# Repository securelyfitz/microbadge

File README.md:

# microbadge
functional badge in 1 square centimeter

The [Shitty Add-On(SAO) spec](https://hackaday.io/project/52950-defcon-26-shitty-add-ons) made it even easier to build badges, boards, and all sorts of assorted flashy swag without the commitment to building a full badge.

To comlpiment the assortment of SAO boards I was working on, I decided to create the smallest possible functional 'badge' with a single SAO connector.

[Hardware design](#hardware-design) will tell you more about how the badge was designed and built. [Other Components](#other-components) will list the other boards available that can be combined to make up a full 'badge'. [Building your Badge](#building-your-badge) covers how to put pieces together and still have a good chance of them working properly. Finally,  [Programming your Badge](#programming-your-badge) covers how to set up the IDE and rewrite the code on your microbadge via USB.

# Stupid SAO tricks
To push the limits of the SAO, I have two example sketches that output mostly-valid IIC data, but manage to push out completely different protocols at the same time.

## IIC Protocol Polyglots
IIC is a two-wire, multi-master protocol. Devices 'claim' the bus with a start condition, and then transmit an address of a slave which is expected to respond. 
However:
1. The start condition prohibits others from speaking
2. everyone is supposed to ignore the data line while clock is low
This means we can do whatever the heck we want with the data line at that point in time. My two POCs are driving Neopixel displays and transmitting UART, potentially for an opticspy to pick it up over an LED.

[NeoPixel Over IIC](https://github.com/securelyfitz/Adafruit_NeoPixel_Over_IIC)

[SAO OpticSpeaker]

# Hardware Design
The microbadge is based on the [Digispark](http://digistump.com/), a small attiny85 badged arduino-compatible development board that uses the [micronucleus usb bootloader](https://github.com/micronucleus/micronucleus).

## Trimming down the design
The fun objective was to see how small the board really could be, while still being programmable with no special hardware:
1. The Digispark had a USB-A connector made from a thick PCB. This took up space and required especially thick boards. I replaced it with a much smaller microUSB header
1. The Digispark has a large 3.3v regulator to power the attiny85 as well as some add-on devices. It also needed zener diodes to make sure the USB data lines did not exceed 3.3v. I removed both. The board no longer gets power from USB and must have an exernal 3.3v power supply
## Adding to the design
1. The Digispark could get power from USB, or from 3.3 or 5v pins. Without the regulator and no room for additional pins, I added pads on the end to edge-mount a vertical cr2032 holder. It's rather difficult to attach and potentially weak unless reinforced, so several battery-bearing add-ons seem to be a better choice.
1. The digispark had a 6-pin header. the SAO header only needs power, ground, and 2 data pins for I2C.

The SAO connector took the most space and is placed on the same side as the necessary resistors and capacitors, while the attiny and usb micro connctor could fit on the other side.

Thanks to a reel of odd-sku attiny85s and parts from china, the BOM cost was under $1 per microbadge (arms/addons excluded). I originally planned to assemble overseas, but when the quoted timeline was weeks longer than I expected, I reached out to [Piotr](https://github.com/esden) and tricked him into helping with assembly. Despite my poor DFM skills, he still managed to get 1100 of them assembled in time for defcoin. Thank [Piotr](https://twitter.com/esden) and/or [1BitSquared](https://twitter.com/1BitSquared)

# Other components
Building the microbadge was inspired by all the add-ons that were available. I started with a series of arms, then added a few faces, and finally a few addons and adapters:
## [Arms](https://github.com/securelyfitz/sao-arms) 
* human
* robo1 - straight roboto arms
* robo2 - bent robot arms
* tent1 - straight tentacles
* tent2 - bent tentacles
* bug1 - straight bug arms
* bug2 - bent bug arms
## [Faces](https://github.com/securelyfitz/sao-faces)
* terminator to terminate your I2C signals with pullups
* badgewife for badgelife diehards
* smiley for dade murphy fans
## Addons/adapters
* [sao-iic](https://github.com/securelyfitz/sao-iic) to attach many common iic breakout boards
* [sao-stripper](https://github.com/securelyfitz/sao-stripper) to attach neopixel strips over SAO
* [sao-flipper](https://github.com/securelyfitz/sao-flipper) to flip a backwards SAO
* [sao-rotate](https://github.com/securelyfitz/sao-rotate) to rotate an sao 90 degrees
* [sao-45](https://github.com/securelyfitz/sao-45) to rotate an sao 45 degrees
## Bonus badges 
* [rpi-shat](https://github.com/securelyfitz/Adafruit-Perma-Proto-HAT-PCB) SAO Hat for raspberry pi
* [hdmi3c](https://github.com/securelyfitz/hdmi3c) hdmi-to-sao version

# Building your Badge
1. Aquire parts. You need:
* a face and a long 4-pin header
* 1 or more arms
* a microbadge
* any other LEDs or addons
* a battery holder for your face or badge
2. Solder the long header onto the backside of your face
3. Solder the appropriate battery holder to your badge (challenging) or the back of your face (much easier)
3. Skewer your arms onto the long header
4. plug the long header onto the microbadge
5. add some LEDs or addons
6. Take a picture and thank [@securelyfitz](https://twitter.com/securelyfitz) and/or [@securinghw](https://twitter.com/securinghw) on twitter.

Due to size, space, and flexibility, the orientations of the headers are not all clearly marked.
## microbadge
Hold the badge with the SAO facing you and the usb port pointed down. VCC is the upper left
## arms
Line one of the arm's SAOs up with the SAO on your badge. The other SAO is wired in the same orientation, so VCC would be upper left on both SAOs no matter how you orient it.
## faces
With the face looking at you, VCC is in the upper left. Remember that the face's SAO port is supposed to be pins on the bottom that attach to the microbadge.

# Programming your Badge
The microbadge is, for all intents and purposes, a digispark clone. The proper micronucleus bootloader and a flashy light firmware has already been flashed.

To get set up, follow the [directions on digispark's website](https://digistump.com/wiki/digispark/tutorials/connecting) to set up your digispark board.

The only difference is that, since the microbadge does NOT get power from usb, it needs a battery to get programmed. The best approach I have found is:
1. remove the battery from your microbadge, or detach the battery-holding face
2. plug in a usb cable to your microbadge
3. click upload in arduino
4. when the prompt says 'Plug in device now', either pop in the battery or attach the face again.

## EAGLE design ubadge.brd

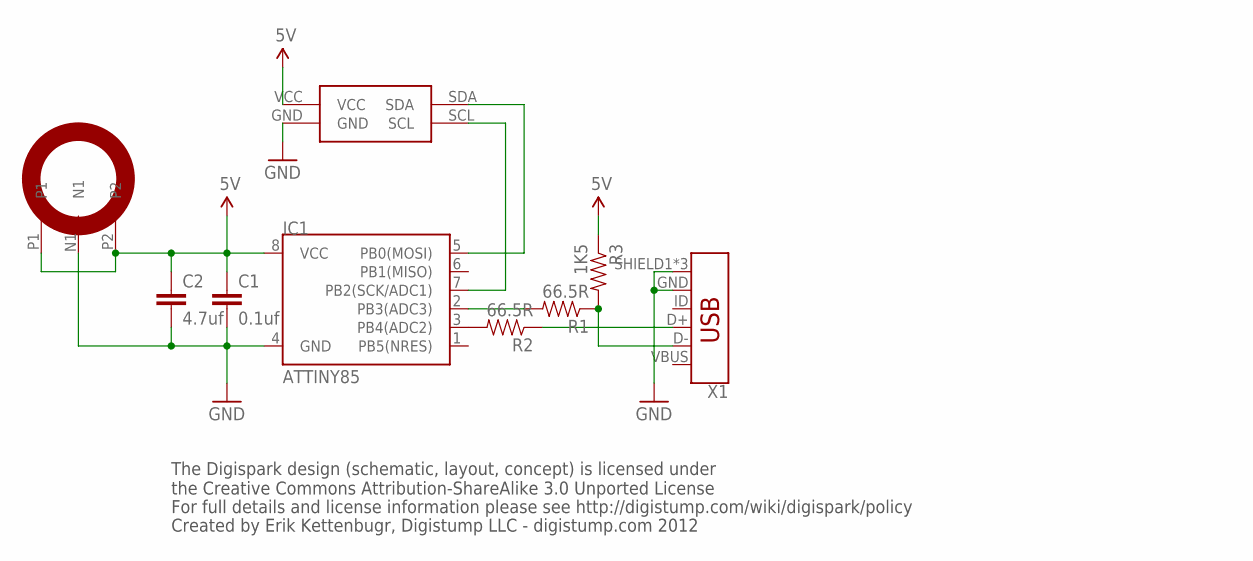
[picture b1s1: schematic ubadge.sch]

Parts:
C1: 0.1uf; 0402-CAP
C2: 4.7uf; 0805
IC1: ATTINY85; SO08-EIAJ
R1, R2: 66.5R; 0402-RES
R3: 1K5; 0402-RES
U$1: SAO-SMT-BOARD; SAO-SMD-BADGE-SOCKET
U$2: CR2032-VERT
X1: USB_MICRO-B_FEMALE-SMT; USB-B-MICRO-SMD

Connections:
DM: R1.1, R3.2, X1.D-
DM-TINY: IC1.2 (PB3(ADC3)), R1.2
DP: R2.1, X1.D+
DP-TINY: IC1.3 (PB4(ADC2)), R2.2
GND: C1.2, C2.2, IC1.4 (GND), U$1.GND, U$2.N1, X1.GND, X1.SHIELD1 (SHIELD), X1.SHIELD2 (SHIELD), X1.SHIELD3 (SHIELD)
SCL: IC1.7 (PB2(SCK/ADC1)), U$1.SCL
SDA: IC1.5 (PB0(MOSI)), U$1.SDA
VBUS: X1.VBUS
VCC: C1.1, C2.1, IC1.8 (VCC), R3.1, U$1.VCC, U$2.P1, U$2.P2

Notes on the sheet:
The Digispark design (schematic, layout, concept) is licensed under the Creative Commons Attribution-ShareAlike 3.0 Unported License
For full details and license information please see http://digistump.com/wiki/digispark/policy
Created by Erik Kettenbugr, Digistump LLC - digistump.com 2012

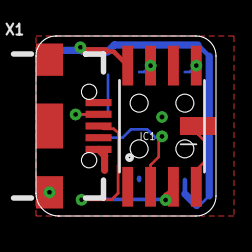
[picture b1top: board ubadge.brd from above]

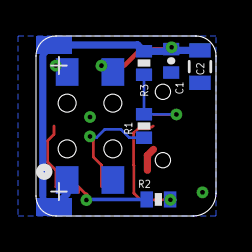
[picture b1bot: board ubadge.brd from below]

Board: 2 copper layers, 10.0 x 10.0 mm, 9 parts (7 on the bottom side), 8 nets.

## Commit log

2018-07-11 initial commit, based on digispark with lots of trim and modification
2018-07-11 fixed mislabled DM/DP (no board change)
2018-07-11 swapped in usb connector with throughole alignment tabs and adjusted a few components. adding centroid, cam, and gerbv files.
2018-08-08 moved final files into hw/sw subdirs
2018-08-08 cleanup

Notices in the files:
parts and their libraries:
SparkFun: Licensing: CC v3.0 Share-Alike You are welcome to use this library for commercial purposes.
SparkFun-Connectors: Licensing: Creative Commons ShareAlike 4.0 International - https://creativecommons.org/licenses/by-sa/4.0
